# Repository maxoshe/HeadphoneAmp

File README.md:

# HeadphoneAmp

In this project I have designed and implemented a Low Noise Headphone Amplifier. The purpose of this project was to gain a better understanding of the design process of printed circuit boards and to practice common engineering tasks such as drafting a schematic, generating a pcb layout from a schematic, generating a bill of materials and soldering components to a PCB.

## Design

The circuit is composed of three smaller circuits, a power supply and two mono
audio channels.
Dividing the entire schematic into three portions helped later with the board layout since I was able to easily separate the power supply from the signal path.

### Power Supply

The power supply receives 15V AC at the input terminal and outputs -15V DC and +15V DC at the output terminals. It achieves the rectification by using a combination of diodes, capacitors, resistors and voltage regulators.

### Audio Channels

Since this is a stereo amplifier, it is crucial to get the gain and signal to noise ratio of each individual mono channel to match. This is why the left and right audio channel schematics are exactly the same. There will still be some small differences since the tolerance of the components can’t be 0% but this difference is hardly noticeable.

The left and right audio channels both receive an audio signal and amplify it using a non inverting amplifier. The operational amplifier that is used in the circuit is a OP275, with two channels on the same IC chip.

## Layout

I’ve placed the power supply components in the upper corner of the board far from the signal path. By doing so I reduced the 60hz noise that can be caused by induction, since the wires carrying 15V AC are far from the wires that carry audio signal.
Another improvement to the layout was to set different trace thickness for power and signal traces.
The majority of the back panel was used as a ground plane. This helps to further reduce noise. For the connections from the PCB to external components I used terminal block plugs, it helped with keeping the design clean and flexible when it comes to connecting and disconnecting external components.

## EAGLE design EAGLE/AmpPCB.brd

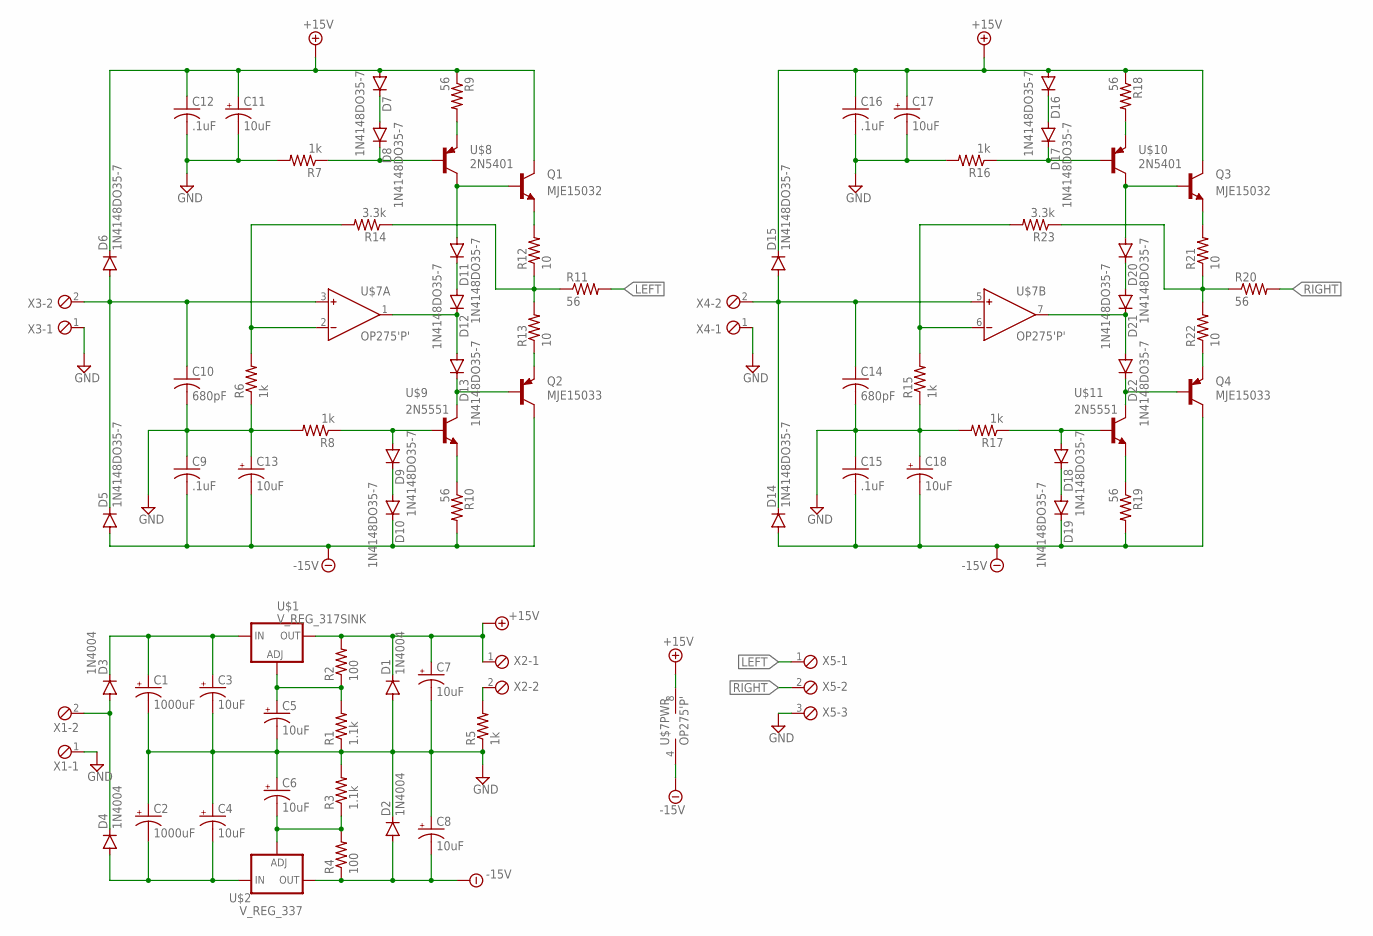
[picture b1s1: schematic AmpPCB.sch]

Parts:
C1, C2: 1000uF; TT5D10
C3, C4, C5, C6, C7, C8, C11, C13, C17, C18: 10uF; E2-5
C9, C12, C15, C16: .1uF; C102-064X133
C10, C14: 680pF; C075-042X103
D1, D2, D3, D4: 1N4004; DO41-10
D5, D6, D7, D8, D9, D10, D11, D12, D13, D14, D15, D16, D17, D18, D19, D20, D21, D22: 1N4148DO35-7; DO35-7
Q1, Q3: MJE15032; TO220V
Q2, Q4: MJE15033; TO220V
R1, R3: 1.1k; 0207/10
R2, R4: 100; 0207/10
R5, R6, R7, R8, R15, R16, R17: 1k; 0207/10
R9, R10, R11, R18, R19, R20: 56; 0207/10
R12, R13, R21, R22: 10; 0207/10
R14, R23: 3.3k; 0207/10
U$1: V_REG_317SINK; TO220-ADJ
U$2: V_REG_337; TO220-ADJ-NEG
U$7: OP275'P'; DIL08
U$8, U$10: 2N5401
U$9, U$11: 2N5551
X1, X2, X3, X4: MPT2; 2POL254
X5: MPT3; 3POL254

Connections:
+15V: C7.+, C11.+, C12.1, C16.1, C17.+, D1.C, D6.C, D7.A, D15.C, D16.A, Q1.2 (C), Q3.2 (C), R2.2, R9.1, R18.1, U$1.OUT, U$7.8 (V+), X2.1
-15V: C8.-, C9.2, C13.-, C15.2, C18.-, D2.A, D5.A, D10.C, D14.A, D19.C, Q2.2 (C), Q4.2 (C), R4.1, R10.2, R19.2, U$2.OUT, U$7.4 (V-)
GND: C1.-, C2.+, C3.-, C4.+, C5.-, C6.+, C7.-, C8.+, C9.1, C10.2, C11.-, C12.2, C13.+, C14.2, C15.1, C16.2, C17.-, C18.+, D1.A, D2.C, R1.1, R3.2, R5.1, R6.1, R7.2, R8.2, R15.1, R16.2, R17.2, X1.1, X3.1, X4.1, X5.3
LEFT: R11.2, X5.1
unnamed: C1.+, C3.+, D3.C, U$1.IN
unnamed: C10.1, D5.C, D6.A, U$7.3 (IN+), X3.2
unnamed: C5.+, R1.2, R2.1, U$1.ADJ
unnamed: R10.1, U$9.E
unnamed: D3.A, D4.C, X1.2
unnamed: C6.-, R3.1, R4.2, U$2.ADJ
unnamed: C2.-, C4.-, D4.A, U$2.IN
unnamed: D9.A, R8.1, U$9.B
unnamed: R5.2, X2.2
unnamed: D9.C, D10.A
unnamed: R6.2, R14.2, U$7.2 (IN-)
unnamed: D13.C, Q2.1 (B), U$9.C
unnamed: D12.C, D13.A, U$7.1 (OUT)
unnamed: D11.C, D12.A
unnamed: Q1.3 (E), R12.2
unnamed: Q2.3 (E), R13.1
unnamed: R11.1, R12.1, R13.2, R14.1
unnamed: D11.A, Q1.1 (B), U$8.C
unnamed: D8.C, R7.1, U$8.B
unnamed: D7.C, D8.A
unnamed: R9.2, U$8.E
unnamed: D18.A, R17.1, U$11.B
unnamed: D18.C, D19.A
unnamed: R15.2, R23.2, U$7.6 (IN-)
unnamed: C14.1, D14.C, D15.A, U$7.5 (IN+), X4.2
unnamed: R19.1, U$11.E
unnamed: D22.C, Q4.1 (B), U$11.C
unnamed: D21.C, D22.A, U$7.7 (OUT)
unnamed: D20.C, D21.A
unnamed: Q4.3 (E), R22.1
unnamed: R20.1, R21.1, R22.2, R23.1
unnamed: Q3.3 (E), R21.2
unnamed: D20.A, Q3.1 (B), U$10.C
unnamed: D17.C, R16.1, U$10.B
unnamed: D16.C, D17.A
unnamed: R18.2, U$10.E
RIGHT: R20.2, X5.2

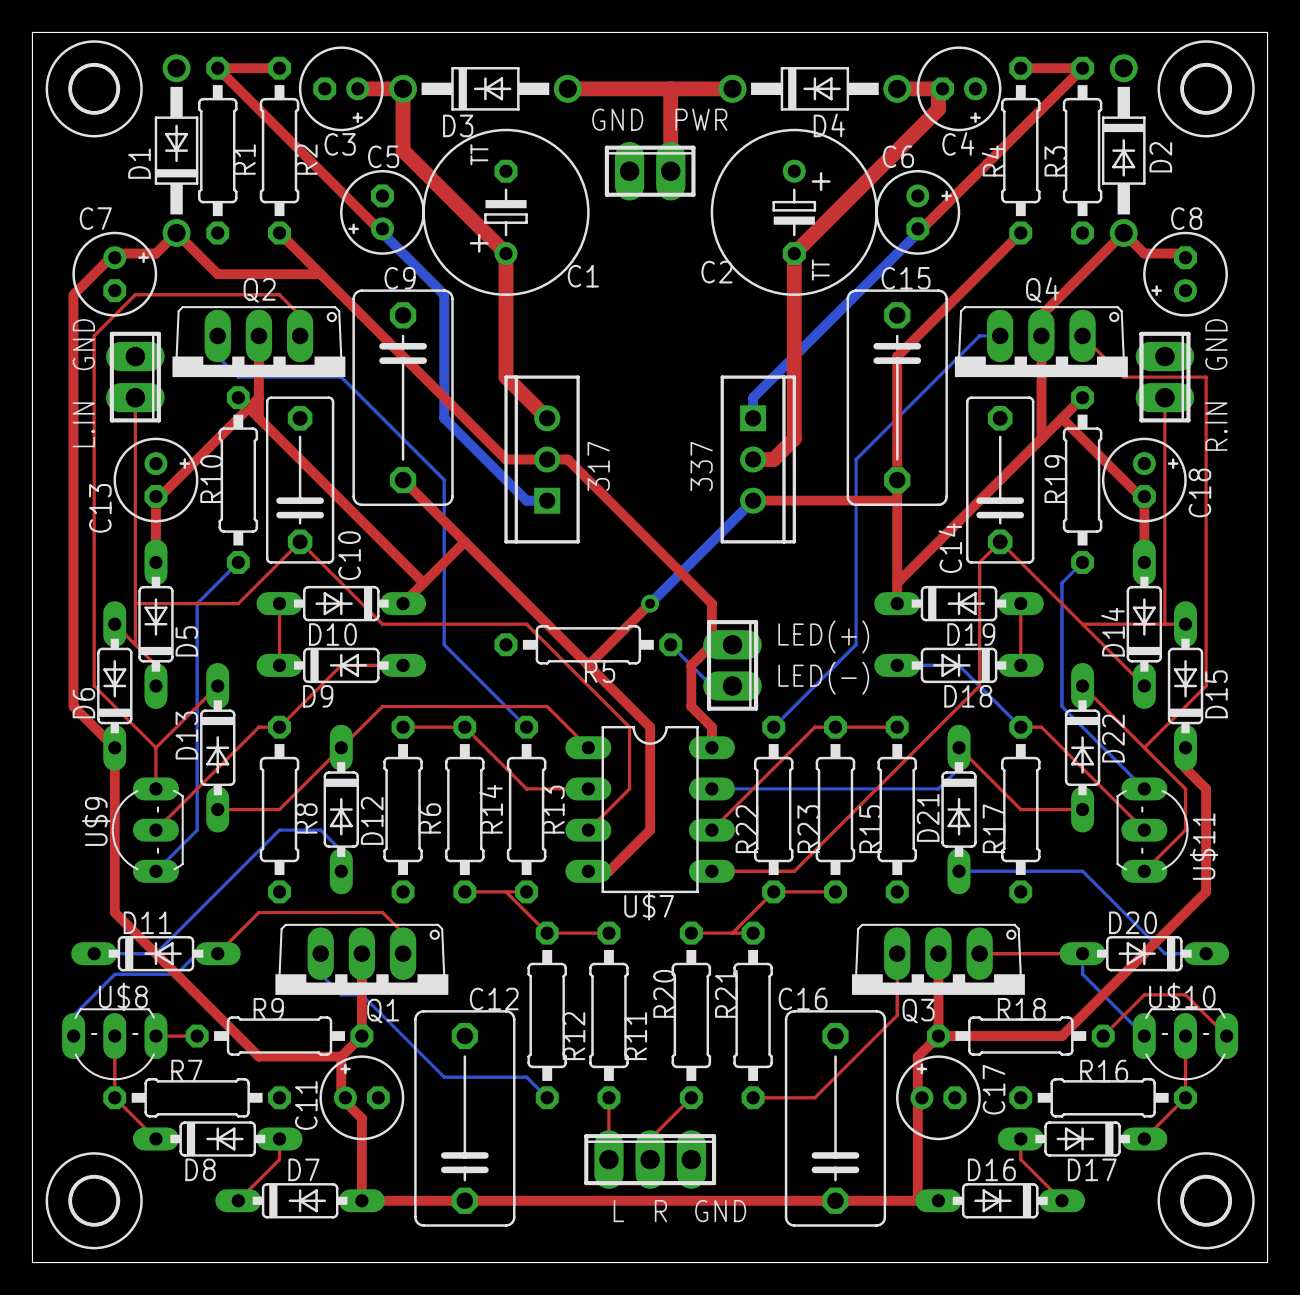
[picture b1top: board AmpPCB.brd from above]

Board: 2 copper layers, 76.2 x 75.9 mm, 83 parts (0 on the bottom side), 41 nets.

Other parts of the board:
U$3, U$4, U$5, U$6: 2,8

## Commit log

2021-05-13 Added design details
2021-05-13 Added EAGLE files
2021-05-13 Added PCB layouts
2021-05-13 Added BOM
2021-05-13 Added photos
2021-06-25 scaled photos
